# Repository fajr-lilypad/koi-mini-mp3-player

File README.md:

# Koi Mini Mp3 Player!
A friendly fish shaped Mp3 player, that sings a tune to cheer you up :)

I came up with this idea when I came across creaters making projects that incorporated audio, and since I don't have as much experience with electrical projects, I thought this would be a fun and educational endeavor. When thinking over what cute designs and shapes I could make this, I became inspired by the friendly koi currency mascot used by hackclub's **fallout** program! I made this project because I wanted to learn more about complex electronics projects, as well as creating something practical that I can use day to day, and I listen to music all the time! And thus, here we are. This will be a helpful and cute tool for listening to tunes on the go, especially when I dont have access to spotify at school hahahaha (i'm **not** crying) (｡T ω T｡)

Some special things I did include making a more complex pcb than I have ever worked with before, along with not following a guided electronics project, so I kinda had to be more independent with troubleshooting and just making decsiions about my own project. In order to use this device, navigate through with a simple screen display to play songs stored on a micro sd card, along using right, left, and select buttons! It very simple to use and assemble. 

# CAD ScreenShots

<table>
  <tr>
    <td>
    
    </td>
    <td>
      
    </td>
    <td>
      
    </td>
  </tr>
</table>

CAD Notes:
- Arduino model in CAD does not match up with footrpint or irl, trust the footprint. it was just the best 3d model I could find.
- This CAD took surprisingly long! It was difficult for me to create a case that fufilled all my criteria, including space, aesthetics, and easy access to the pcb for simple troubleshooting. I ended up going with this design, but not after making several rough drafts of potential cases. I'm happy with this one, as it includes snap fit joints, a hole for the headphone jack, and is overall super cute :)
- The most difficult parts of this was the parts that nobody notices, mounting holes lol. took a while to align, but I'm sure most people are more efficient at cad than i am!

# PCB ScreenShots

<table>
  <tr>
    <td rowspan="2">
      
    </td>
    <td>
      
    </td>
  </tr>
  <tr>
    <td>
      
    </td>
  </tr>
</table>

PCB Notes:
- The PCB took me a **while**. It took 6 versions to come up with the final draft. The biggest difficulty was deciding a layout that would be easy to work with and troubleshoot, along with research into which components I should use. I had to learn how to do a lot of new things in KiCad, including making my own symbols!
- For structure, I created a blank PCB with the same shape attached to the bottom of the real pcb with brass standoffs. I found in my research that this is common when creating mp3 players, along with custom PCBs in general. After running into trouble with mounting, I scrapped that idea. Now, the there is just one pcb secured with standoffs.

## Schematic ScreenShot

# Zine !!

# Build Guide

Assembly for this Fish MP3 Player isn't too complicated. To start off, once components have arrived, be sure that your code is ready. When assembling components, I plan on starting out with a breadboard to test firmware before soldering, and be sure to secure the bottom blank pcb with standoffs. In the meantime, get the 3d printer started on the case top, bottom, and fins! The snap fit joints should make the case easy to work with, so it isnt hard to access the pcb.

## Firmware

I customized code for the display from Pcbcupid soundpod and used a butmap converter to display the images! Download whatever songs you'd like to be played on a micro sd card, and program to navigate through the files with the Pcbcupid reference mentioned earlier.

## BOM

| Item | Purpose | Price | Source | Link |
|---|---|---|---|---|
| Arduino Pro Mini | Microcontroller | $1.66 | AliExpress | https://www.aliexpress.us/item/3256809225264759.html?spm=a2g0o.productlist.main.8.1154d373WriJct&aem_p4p_detail=202606041608381516129101675990000653758&algo_pvid=17235d99-b4bf-4eae-8822-effcf9c3d7d6&algo_exp_id=17235d99-b4bf-4eae-8822-effcf9c3d7d6-7&pdp_ext_f=%7B%22order%22%3A%22975%22%2C%22eval%22%3A%221%22%2C%22fromPage%22%3A%22search%22%7D&pdp_npi=6%40dis%21USD%213.01%210.99%21%21%2120.29%216.68%21%402103212317806145181028917e7e75%2112000049016718294%21sea%21US%210%21ABX%211%210%21n_tag%3A-29910%3Bd%3A5ad2bf3%3Bm03_new_user%3A-29895%3BpisId%3A5000000207178484&curPageLogUid=sAWeRD3Rte4l&utparam-url=scene%3Asearch%7Cquery_from%3A%7Cx_object_id%3A1005009411579511%7C_p_origin_prod%3A&search_p4p_id=202606041608381516129101675990000653758_2&_gl=1*1og3qna*_gcl_aw*R0NMLjE3ODA1ODg3MzAuQ2p3S0NBand4SVRSQmhCWUVpd0E2bVptN1gyMmhLYmcxNEFXTzJqMzVocGFuYXA0Yjk1M2prS2RFd1JhSVdJU2VTWEpSTl9ReDRidUZSb0NfRDRRQXZEX0J3RQ..*_gcl_dc*R0NMLjE3ODA1ODg3MzAuQ2p3S0NBand4SVRSQmhCWUVpd0E2bVptN1gyMmhLYmcxNEFXTzJqMzVocGFuYXA0Yjk1M2prS2RFd1JhSVdJU2VTWEpSTl9ReDRidUZSb0NfRDRRQXZEX0J3RQ..*_gcl_au*MTczMjcyMzY2MS4xNzgwMDc1MDcx*_ga*OTI3ODgwMTQ2MTkzMTUxLjE3NjY3MjAwNzk4MjQ.*_ga_VED1YSGNC7*czE3ODA2MTQ1MTkkbzEwJGcwJHQxNzgwNjE0NTE5JGo2MCRsMCRoMA.. |
| DFPlayer Mini | Audio Module | $0.73 | AliExpress | https://www.aliexpress.us/item/3256806817772564.html?src=google&src=google&albch=shopping&acnt=708-803-3821&isdl=y&slnk=&plac=&mtctp=&albbt=Google_7_shopping&aff_platform=google&aff_short_key=UneMJZVf&gclsrc=aw.ds&albagn=888888&ds_e_adid=&ds_e_matchtype=&ds_e_device=c&ds_e_network=x&ds_e_product_group_id=&ds_e_product_id=en3256806817772564&ds_e_product_merchant_id=5347193707&ds_e_product_country=US&ds_e_product_language=en&ds_e_product_channel=online&ds_e_product_store_id=&ds_url_v=2&albcp=19558607238&albag=&isSmbAutoCall=false&needSmbHouyi=false&gad_source=1&gad_campaignid=19566915268&gbraid=0AAAAAD6I-hH4f_RBPgk4-7deK7YYKAQBI&gclid=Cj0KCQjw2_TQBhCnARIsAF3-XhwdQfZYBiIl5K6vnZvOP9pSz2Zze0GxJHst8n-6nMQRg2g9PXQ3k2kaAlETEALw_wcB&gatewayAdapt=glo2usa |
| 1.3 in OLED | Display Screen | $0.99 | AliExpress | https://www.aliexpress.us/item/3256809997650807.html?spm=a2g0o.detail.pcDetailTopMoreOtherSeller.1.44a4LJzILJzIhe&gps-id=pcDetailTopMoreOtherSeller&scm=1007.40050.354490.0&scm_id=1007.40050.354490.0&scm-url=1007.40050.354490.0&pvid=19e49a3f-77e4-4718-aa90-6f56865ac08a&_t=gps-id%3ApcDetailTopMoreOtherSeller%2Cscm-url%3A1007.40050.354490.0%2Cpvid%3A19e49a3f-77e4-4718-aa90-6f56865ac08a%2Ctpp_buckets%3A668%232846%238110%231995&pdp_ext_f=%7B%22order%22%3A%22149%22%2C%22eval%22%3A%221%22%2C%22sceneId%22%3A%2230050%22%2C%22fromPage%22%3A%22recommend%22%7D&pdp_npi=6%40dis%21USD%219.21%210.99%21%21%2161.95%216.64%21%402101e81117803697190038799ea8cd%2112000051437252681%21rec%21US%21%21ABX%211%210%21n_tag%3A-29910%3Bd%3A3d07d826%3Bm03_new_user%3A-29895%3BpisId%3A5000000207178484&utparam-url=scene%3ApcDetailTopMoreOtherSeller%7Cquery_from%3A%7Cx_object_id%3A1005010183965559%7C_p_origin_prod%3A |
| TRS Female Headphone Jack | Audio output | $1.15 | DigiKey | https://shorturl.at/xDjAV | 
| 3.7 V Battery | Power | $4.18 | AliExpress | https://www.aliexpress.us/item/3256808681500642.html?spm=a2g0o.productlist.main.15.4bb1241e7b8vlw&algo_pvid=f988d292-1588-4233-b59b-e6f268a99bd2&algo_exp_id=f988d292-1588-4233-b59b-e6f268a99bd2-14&pdp_ext_f=%7B%22order%22%3A%22803%22%2C%22eval%22%3A%221%22%2C%22fromPage%22%3A%22search%22%7D&pdp_npi=6%40dis%21USD%2112.82%214.57%21%21%2186.37%2130.74%21%40210328d417805887373364721ef74a%2112000047018637633%21sea%21US%210%21ABX%211%210%21n_tag%3A-29910%3Bd%3A3d07d826%3Bm03_new_user%3A-29895%3BpisId%3A5000000208023469&curPageLogUid=Fx9M4p2WWRIq&utparam-url=scene%3Asearch%7Cquery_from%3A%7Cx_object_id%3A1005008867815394%7C_p_origin_prod%3A |
| 2 pin JST Battery Connector | Battery Connector | $3.90 | Aliexpress| https://shorturl.at/0xLe1 |
| Micro SD Card | Store songs | $1.13 | AliExpress | https://www.aliexpress.com/ssr/300000512/BundleDeals2?spm=a2g0o.productlist.main.1.63ad5328tH0Kby&productIds=1005010775019515%3A12000053469023885&pha_manifest=ssr&_immersiveMode=true&disableNav=YES&sourceName=SEARCHProduct&utparam-url=scene%3Asearch%7Cquery_from%3A%7Cx_object_id%3A1005010775019515%7C_p_origin_prod%3A&pvid=63c826e6-f28e-4320-818e-ceaa5da16f6c&_gl=1*17p9z8x*_gcl_aw*R0NMLjE3ODA1ODg3MzAuQ2p3S0NBand4SVRSQmhCWUVpd0E2bVptN1gyMmhLYmcxNEFXTzJqMzVocGFuYXA0Yjk1M2prS2RFd1JhSVdJU2VTWEpSTl9ReDRidUZSb0NfRDRRQXZEX0J3RQ..*_gcl_dc*R0NMLjE3ODA1ODg3MzAuQ2p3S0NBand4SVRSQmhCWUVpd0E2bVptN1gyMmhLYmcxNEFXTzJqMzVocGFuYXA0Yjk1M2prS2RFd1JhSVdJU2VTWEpSTl9ReDRidUZSb0NfRDRRQXZEX0J3RQ..*_gcl_au*MTczMjcyMzY2MS4xNzgwMDc1MDcx*_ga*OTI3ODgwMTQ2MTkzMTUxLjE3NjY3MjAwNzk4MjQ.*_ga_VED1YSGNC7*czE3ODA1ODg3MjAkbzkkZzEkdDE3ODA1ODg4NDEkajIyJGwwJGgw |
| Micro Push Buttons | Inputs | $0.33 | Same Sky | https://www.sameskydevices.com/product/switches/tactile-switches/ts24-62-14-bl-250-smt-tr-67 |
| Custom Tactile Buttons | Comfort | $0 | 3D Printed |
| Custom Koi Case | Aesthetics | $0 | 3D Printed |
| Breadboard | testing | $0.55 | AliExpress | https://shorturl.at/7gDRe |
| Custom PCB | PCB | $5.30 | JLCPCB |
| Brass PCB standoffs | Supports structure | $0.99 | AliExpress | https://shorturl.at/dPENK |
| Soldering Iron | Assembly | $0 | Owned |
| 3D Printer | Case Manufacturing | $0 | Owned |
| Wired Headphones | Audio Output | $0 | Owned |
|  |  |  |  | **Subtotal: $20.91 USD**  |

## Notes and Acknowledgments
- Thank you to **Hackclub** and the **Fallout team** for making this project possible! It's because of you that I was inspired and able to make this project!
- Thank you to the user Digiicam for helpful inspo for wiring and components!
- Thank you to Pcbcupid for simple customizable firmware!

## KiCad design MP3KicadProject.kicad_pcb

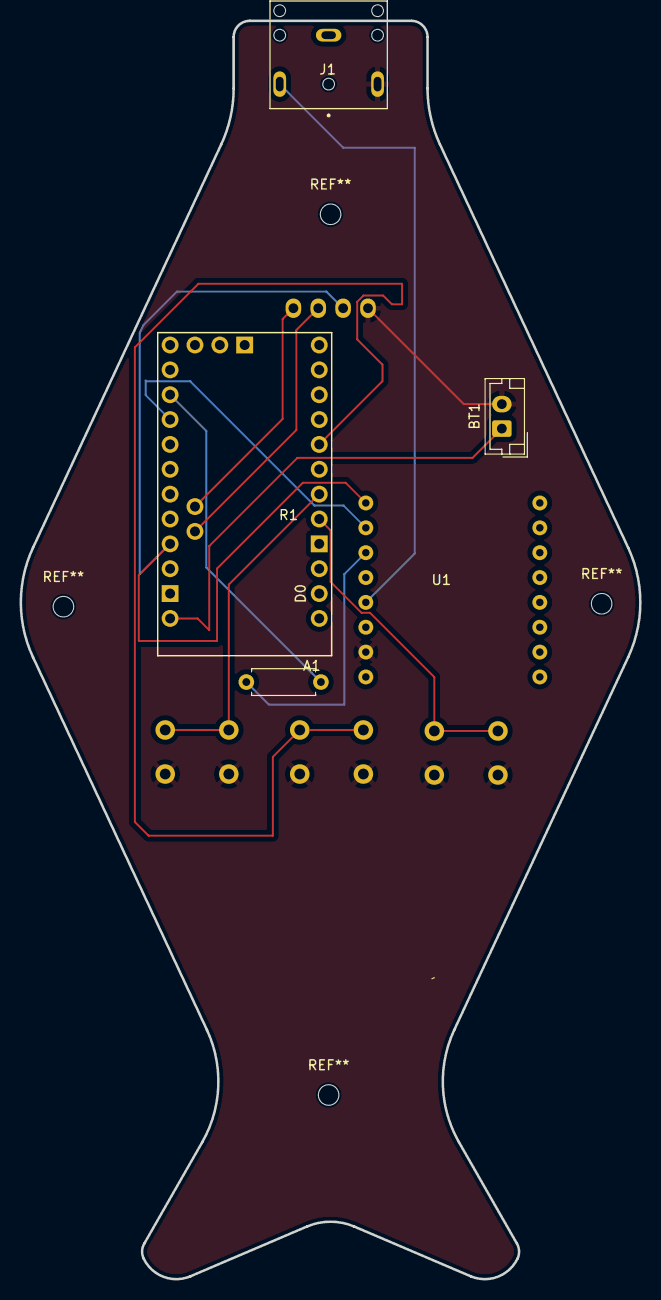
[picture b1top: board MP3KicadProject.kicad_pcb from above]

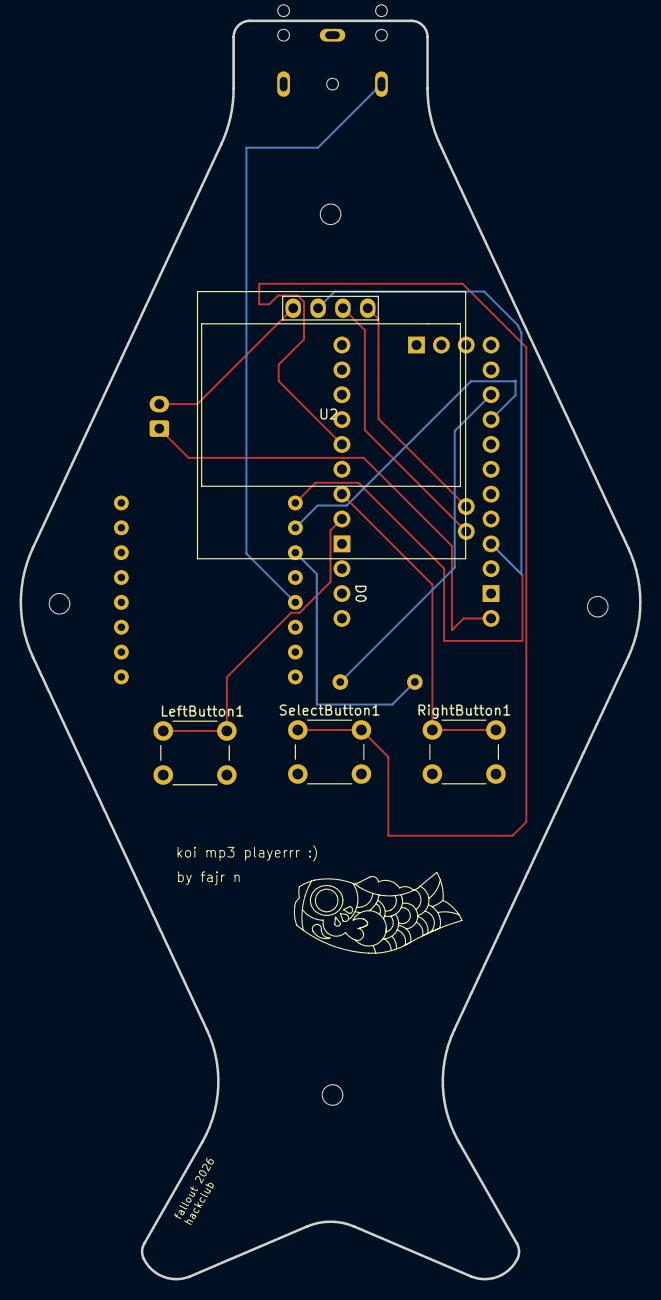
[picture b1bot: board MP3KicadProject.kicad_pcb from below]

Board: 2 copper layers, 63.3 x 128.6 mm, 9 parts (4 on the bottom side), 12 nets.

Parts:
A1: Arduino Pro Mini; Clone_Pro_Mini_Socket_NoSPH
BT1: Battery_Cell; JST_EH_B2B-EH-A_1x02_P2.50mm_Vertical
J1: female headphone jack; CUI_SJ1-3523N
LeftButton1: SW_Push; SW_PUSH_6mm
R1: Resistor; R_Axial_DIN0207_L6.3mm_D2.5mm_P7.62mm_Horizontal
RightButton1: SW_Push; SW_PUSH_6mm
SelectButton1: SW_Push; SW_PUSH_6mm
U1: df mini player; DFPlayer
U2: 1.3 Oled Screen; 128x64OLED

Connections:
+BATT: A1.RAW, BT1.1 (+)
GND: BT1.2 (-), J1.3, LeftButton1.2, RightButton1.2, SelectButton1.2, U1.7 (GND), U2.1 (GND)
unnamed: A1.A4 (A4/SDA), U2.4 (SDA)
unnamed: A1.A5 (A5/SCL), U2.3 (SCL)
unnamed: A1.D2 (D2_INT0), LeftButton1.1
unnamed: A1.D3 (D3_INT1), RightButton1.1
unnamed: A1.D12 (D12_MISO), R1.2
unnamed: A1.D13 (D13_SCK), U1.2 (RX)
unnamed: A1.D5, SelectButton1.1
unnamed: A1.Vcc1 (Vcc), U1.1 (VCC), U2.2 (VCC_IN)
unnamed: J1.2, U1.5 (DAC_L)
unnamed: R1.1, U1.3 (TX)

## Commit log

2026-05-29 Create BOM
2026-05-29 Update BOM
    headphones
2026-05-29 Create Schematic
2026-05-29 Create PCB
2026-05-29 Update BOM
2026-05-29 Rename BOM to BOM.md
2026-06-02 Rename MP3KicadProject.kicad_pro to PCB/MP3KicadProject.kicad_pro
2026-06-02 Rename MP3KicadProject.kicad_sch to PCB/MP3KicadProject.kicad_sch
2026-06-02 Rename MP3KicadProject.kicad_pcb to PCB/MP3KicadProject.kicad_pcb
2026-06-02 Rename MP3KicadProject-PTH.zip to PCB/MP3KicadProject-PTH.zip
2026-06-02 Rename Screenshot 2026-06-01 223904.png to PCB/Schematic.png
2026-06-02 Rename Screenshot 2026-06-01 223904.png to Schematic/Screenshot 2026-06-01 223904.png
2026-06-02 Rename Screenshot 2026-06-01 203631.png to PCBScreenshot_3DViewer.png
2026-06-02 Rename Screenshot 2026-06-01 203654.png to ScreenshotPCB_3DViewer_SideB.png
2026-06-03 Rename Koi Case Assembly.step to CAD/Case/Koi Case Assembly.step
2026-06-03 Rename Koi Case Bottom.step to CAD/Case/Koi Case Bottom.step
2026-06-03 Rename Koi Case Top.step to CAD/Case/Koi Case Top.step
2026-06-03 Rename CAD/Mp3 PCB CAD Assembly.f3z to CAD/PCB Cad/Mp3 PCB CAD Assembly.f3z
2026-06-03 Rename CAD/MP3 CAD PCB.step to CAD/PCB Cad/MP3 CAD PCB.step
2026-06-03 Rename MP3 CAD PCB.step to MP3 PCB.step
2026-06-03 Rename Mp3 PCB CAD Assembly.f3z to Mp3 PCB Assembly.f3z
2026-06-03 Rename CAD/PCB Cad/SSD1306_OLED_Display(128x64).step to CAD/PCB Cad/Electronics/Adafruit SSD1306 1.3in OLED Display.step
2026-06-03 Rename DFR0299--3DModel-STEP-56544.STEP to DF Player Mini.STEP
2026-06-03 Rename Jack 3_5 mm TRS femaile.step to Headphone Jack 3.5 mm TRS female.step
2026-06-03 Rename ASSEMBLY.SLDASM to Arduino Pro Mini.step
2026-06-04 Rename fish mp3 player.pdf to Fish Mp3 Zine.pdf
2026-06-04 Rename BOM.md to BOM.csv
